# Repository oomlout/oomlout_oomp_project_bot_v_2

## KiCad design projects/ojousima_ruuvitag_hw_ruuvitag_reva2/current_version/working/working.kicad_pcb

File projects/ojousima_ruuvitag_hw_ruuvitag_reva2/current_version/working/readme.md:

# ruuvitag_hw
 
## summary 
* id: ojousima_ruuvitag_hw_ruuvitag_reva2
* user: ojousima
* name: ruuvitag_hw
* board: ruuvitag_reva2
* repo: https://github.com/ojousima/ruuvitag_hw
* src_file_repo_kicad_pcb: ruuvitag_reva2/ruuvitag_reva2.kicad_pcb
* src_file_repo_kicad_pcb_link: https://github.com/ojousima/ruuvitag_hw/tree/master/ruuvitag_reva2/ruuvitag_reva2.kicad_pcb

* src_file_repo_sch: ruuvitag_reva2/ruuvitag_reva2.sch
* src_file_repo_sch_link: https://github.com/ojousima/ruuvitag_hw/tree/master/ruuvitag_reva2/ruuvitag_reva2.sch
* full details link: https://github.com/oomlout/oomlout_oomp_project_bot_v_2/tree/main/projects/ojousima_ruuvitag_hw_ruuvitag_reva2/current_version/working

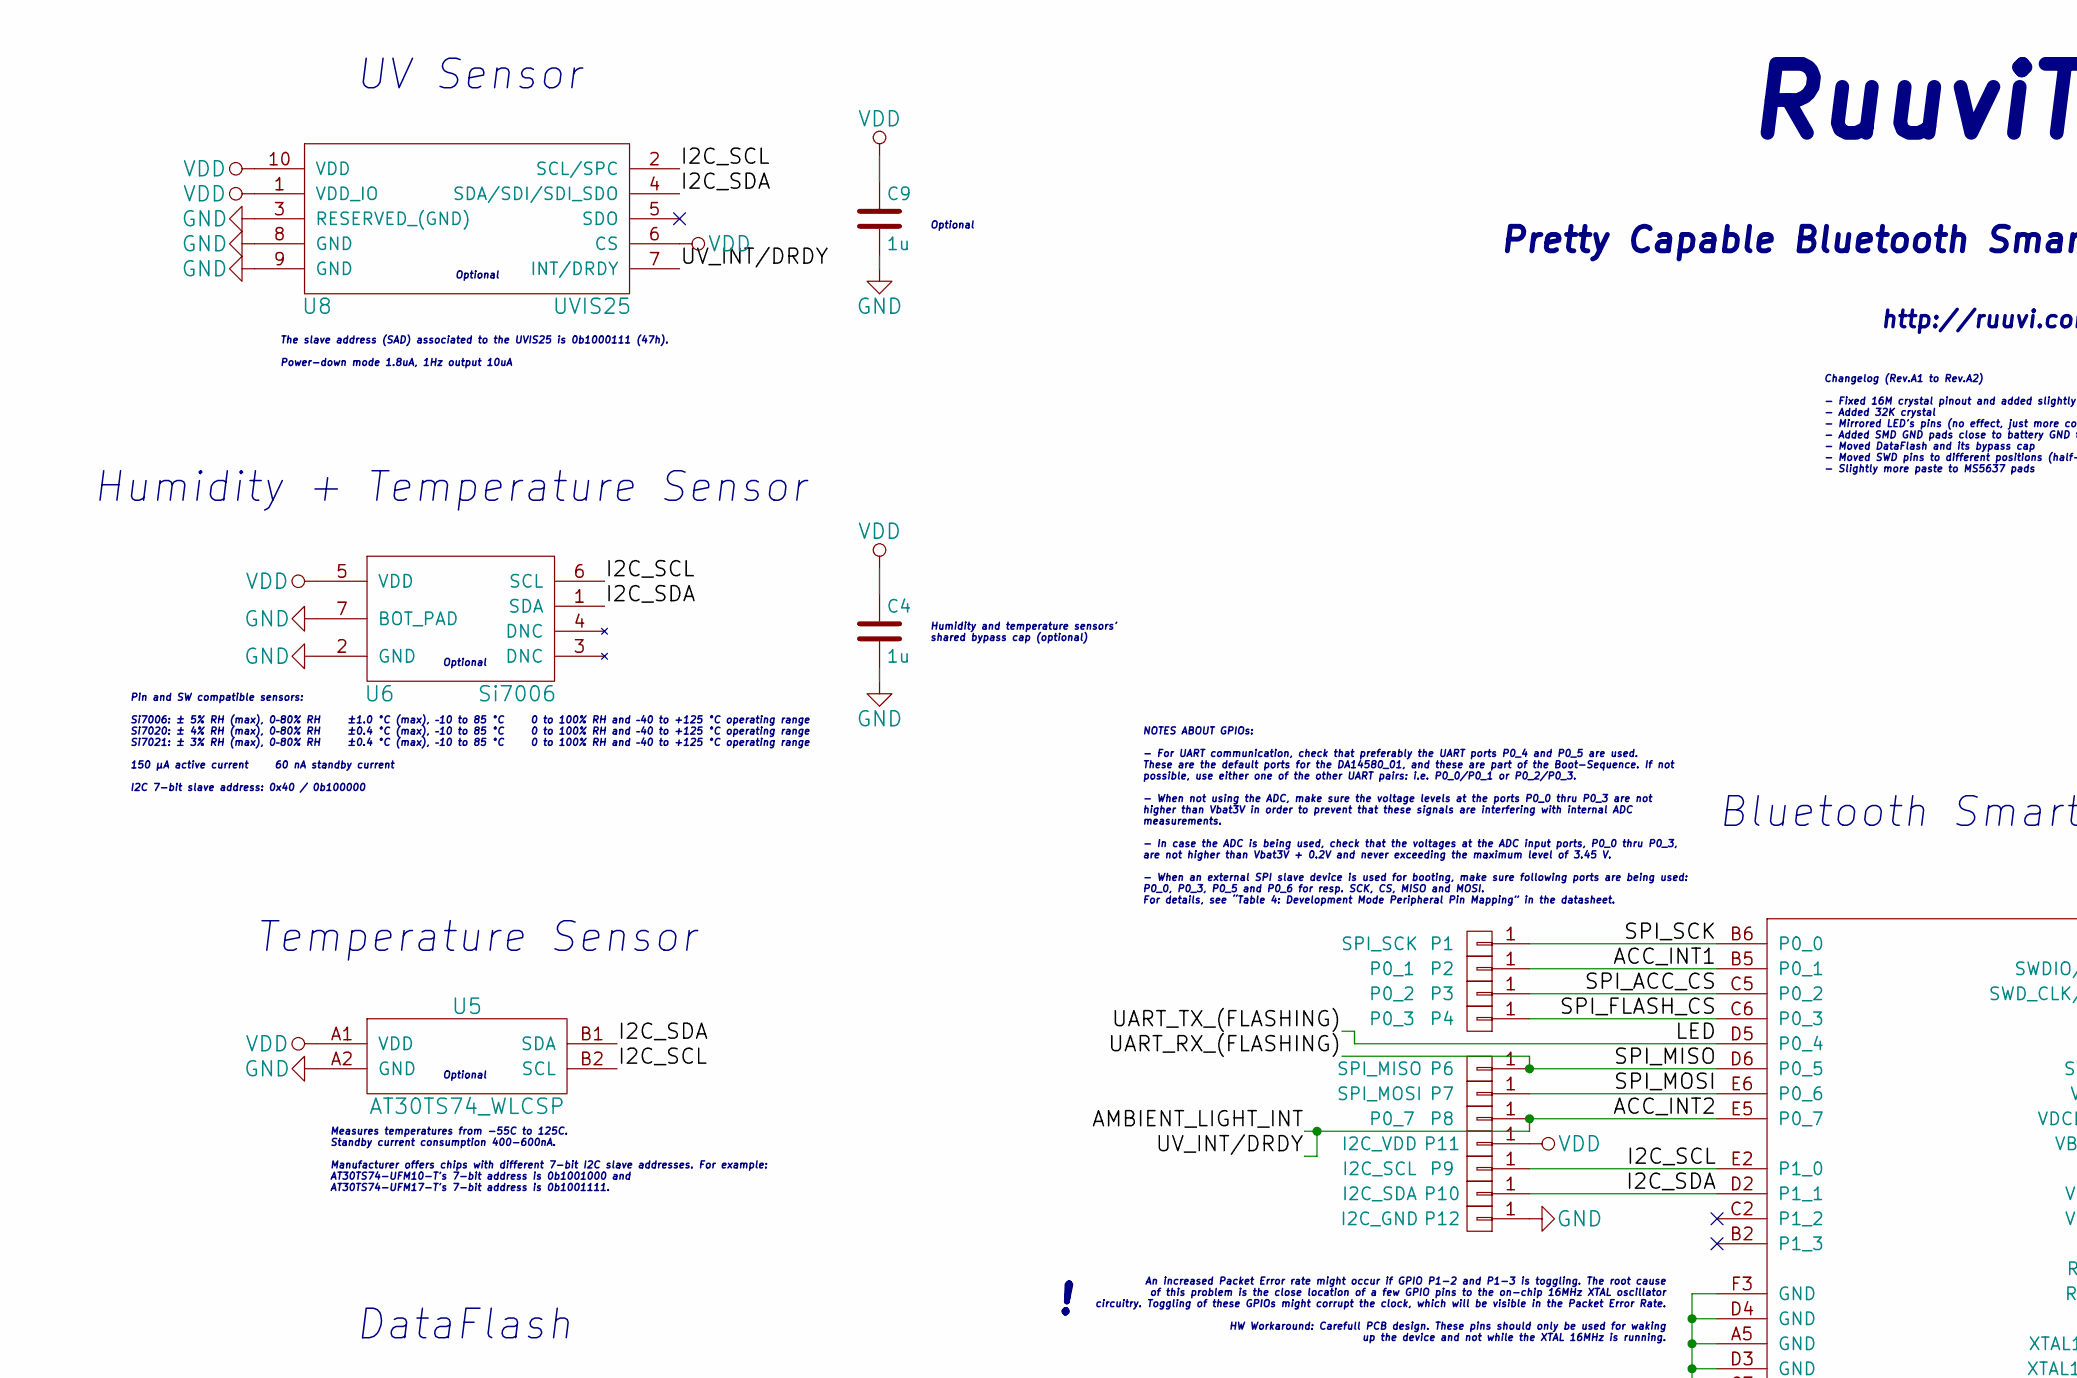
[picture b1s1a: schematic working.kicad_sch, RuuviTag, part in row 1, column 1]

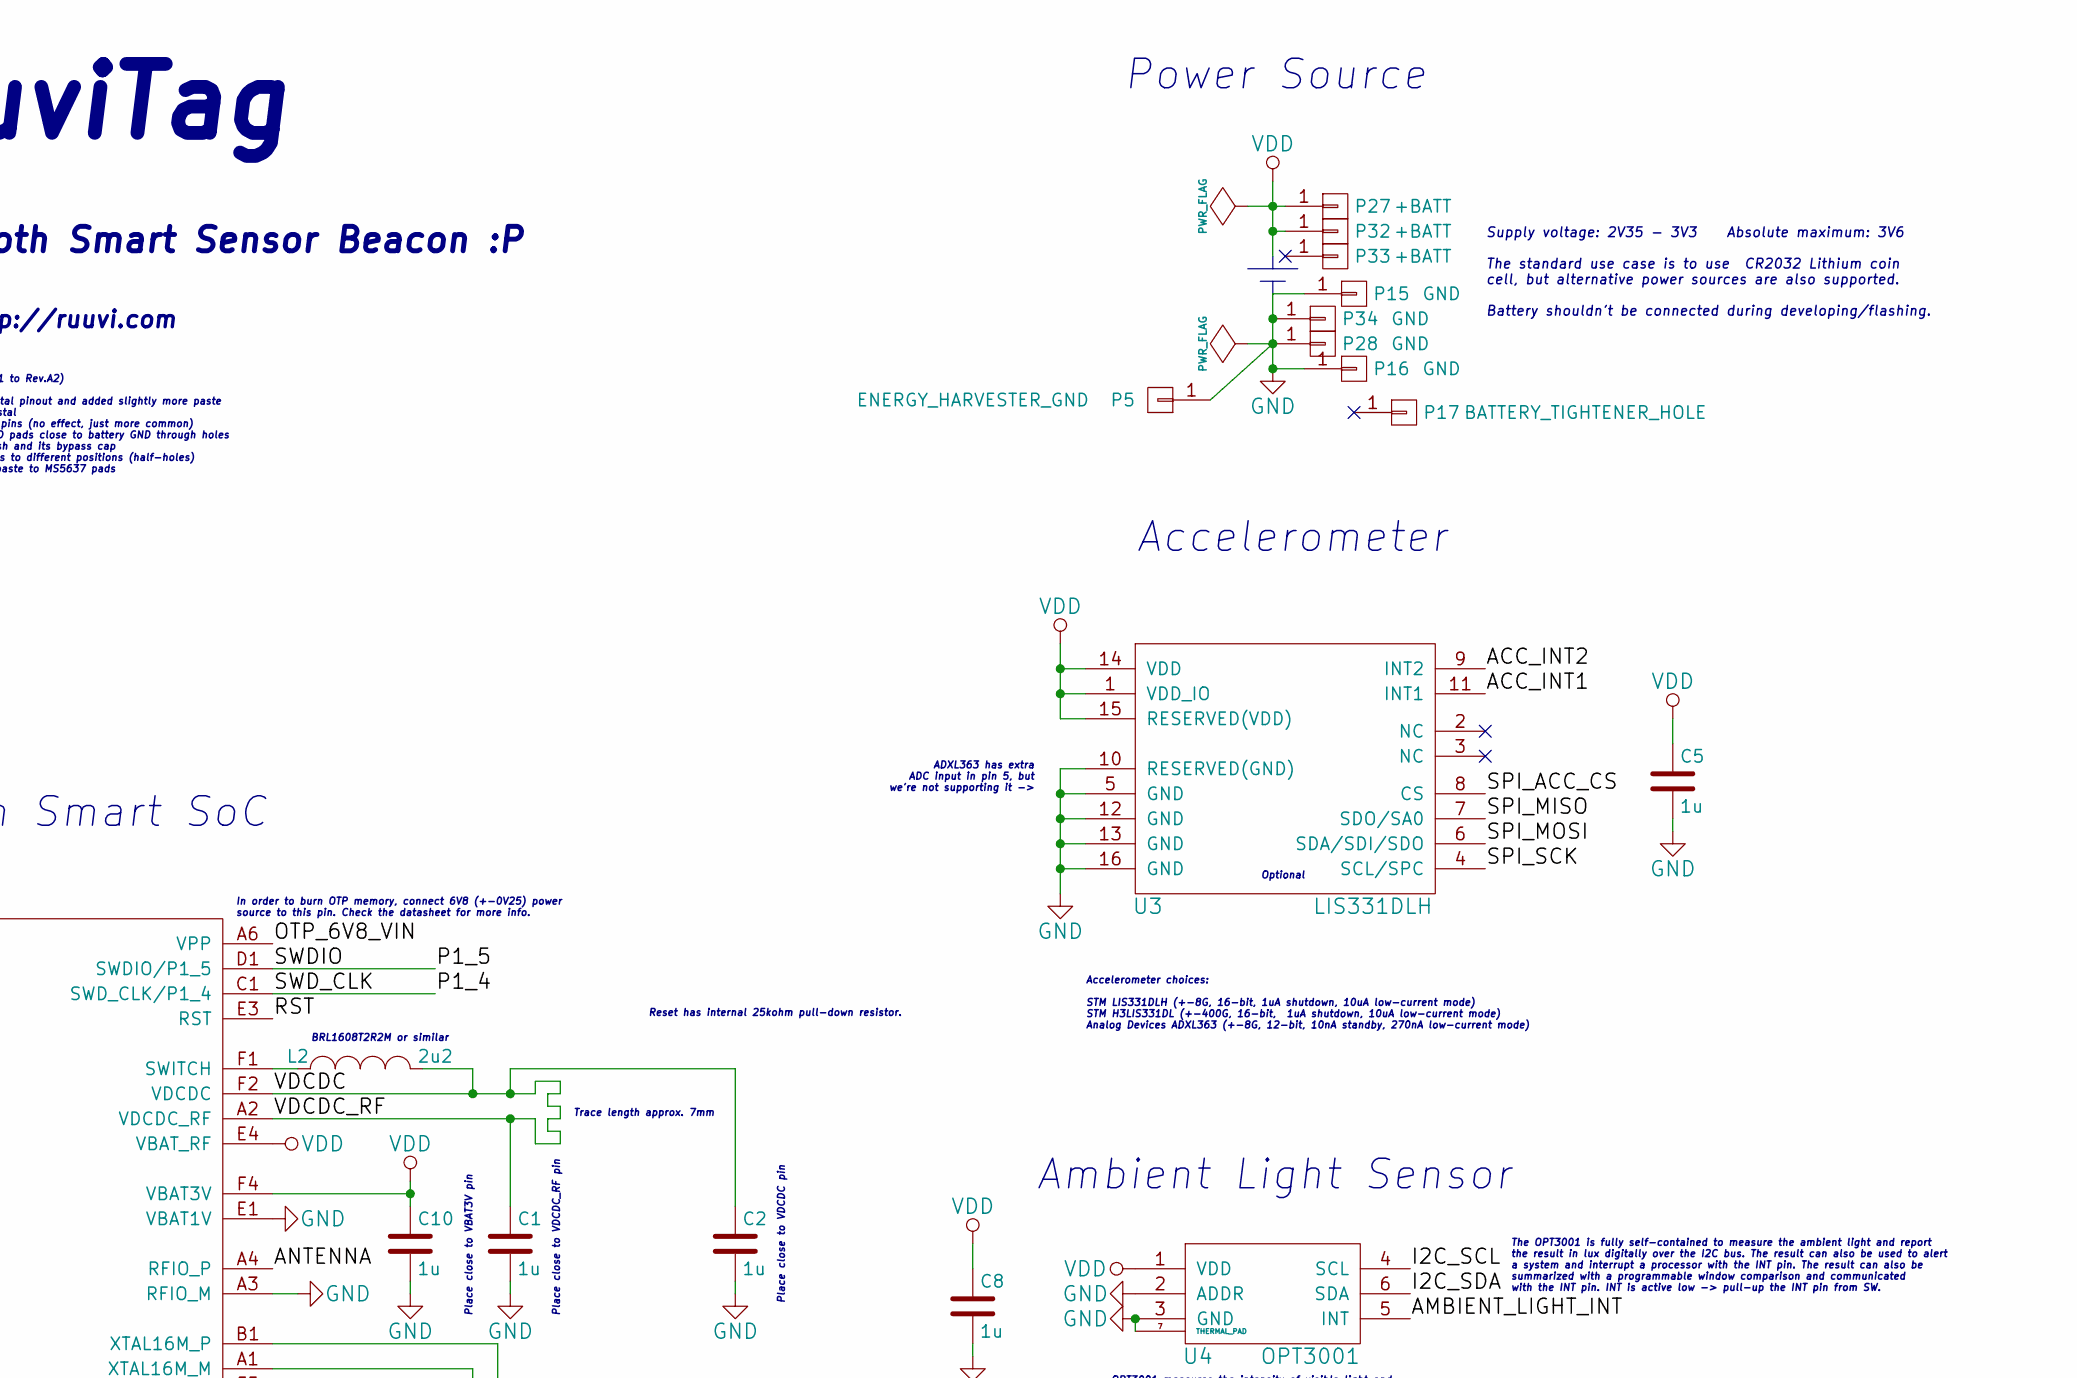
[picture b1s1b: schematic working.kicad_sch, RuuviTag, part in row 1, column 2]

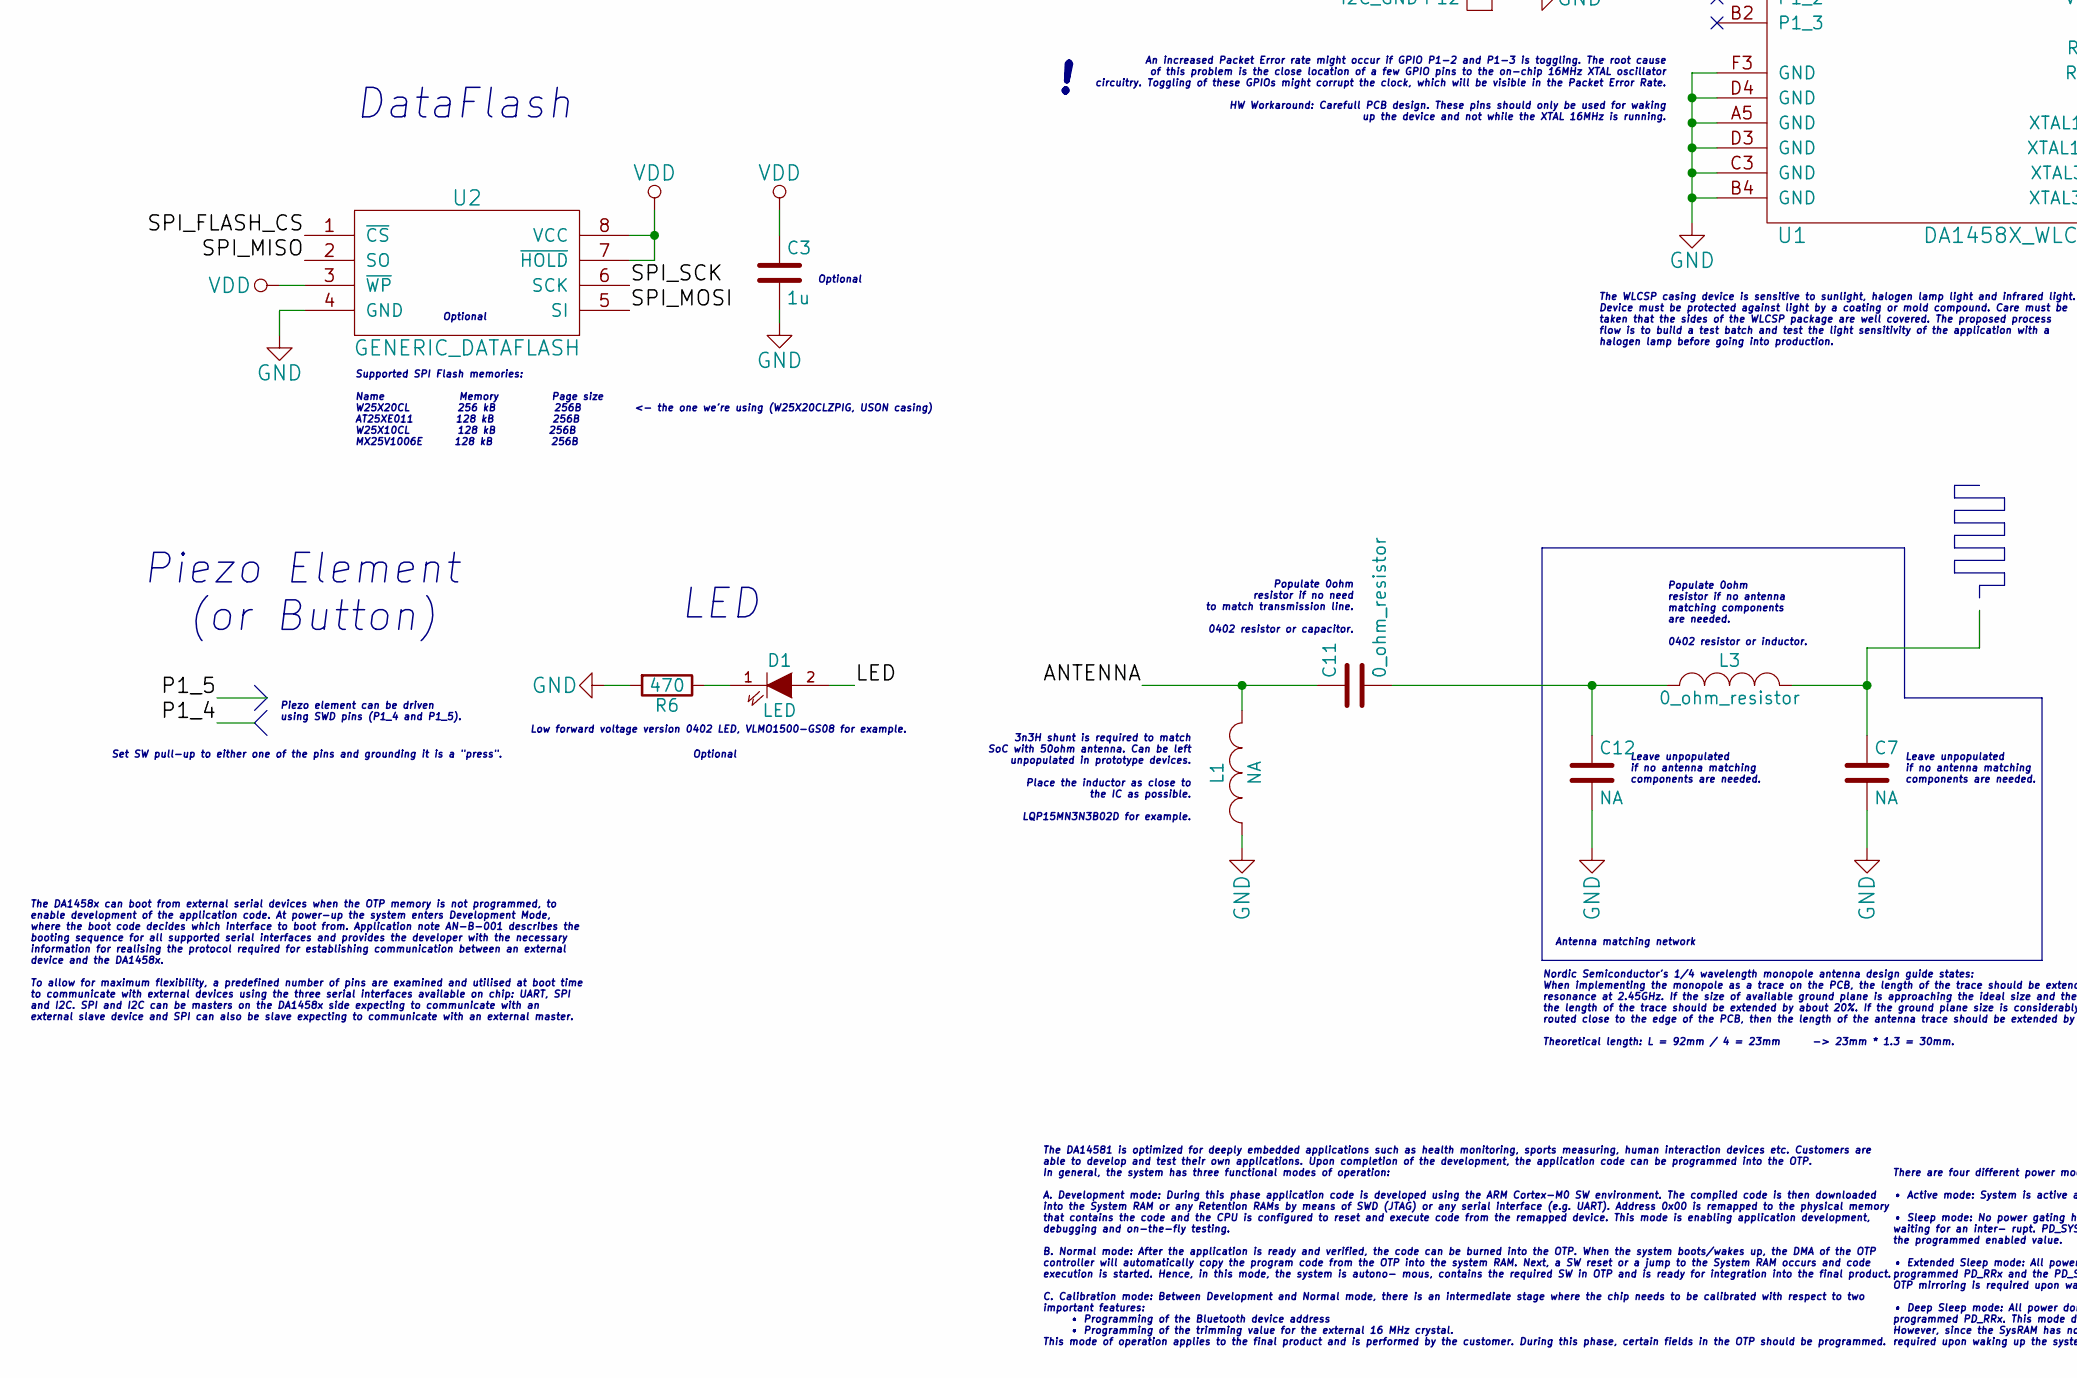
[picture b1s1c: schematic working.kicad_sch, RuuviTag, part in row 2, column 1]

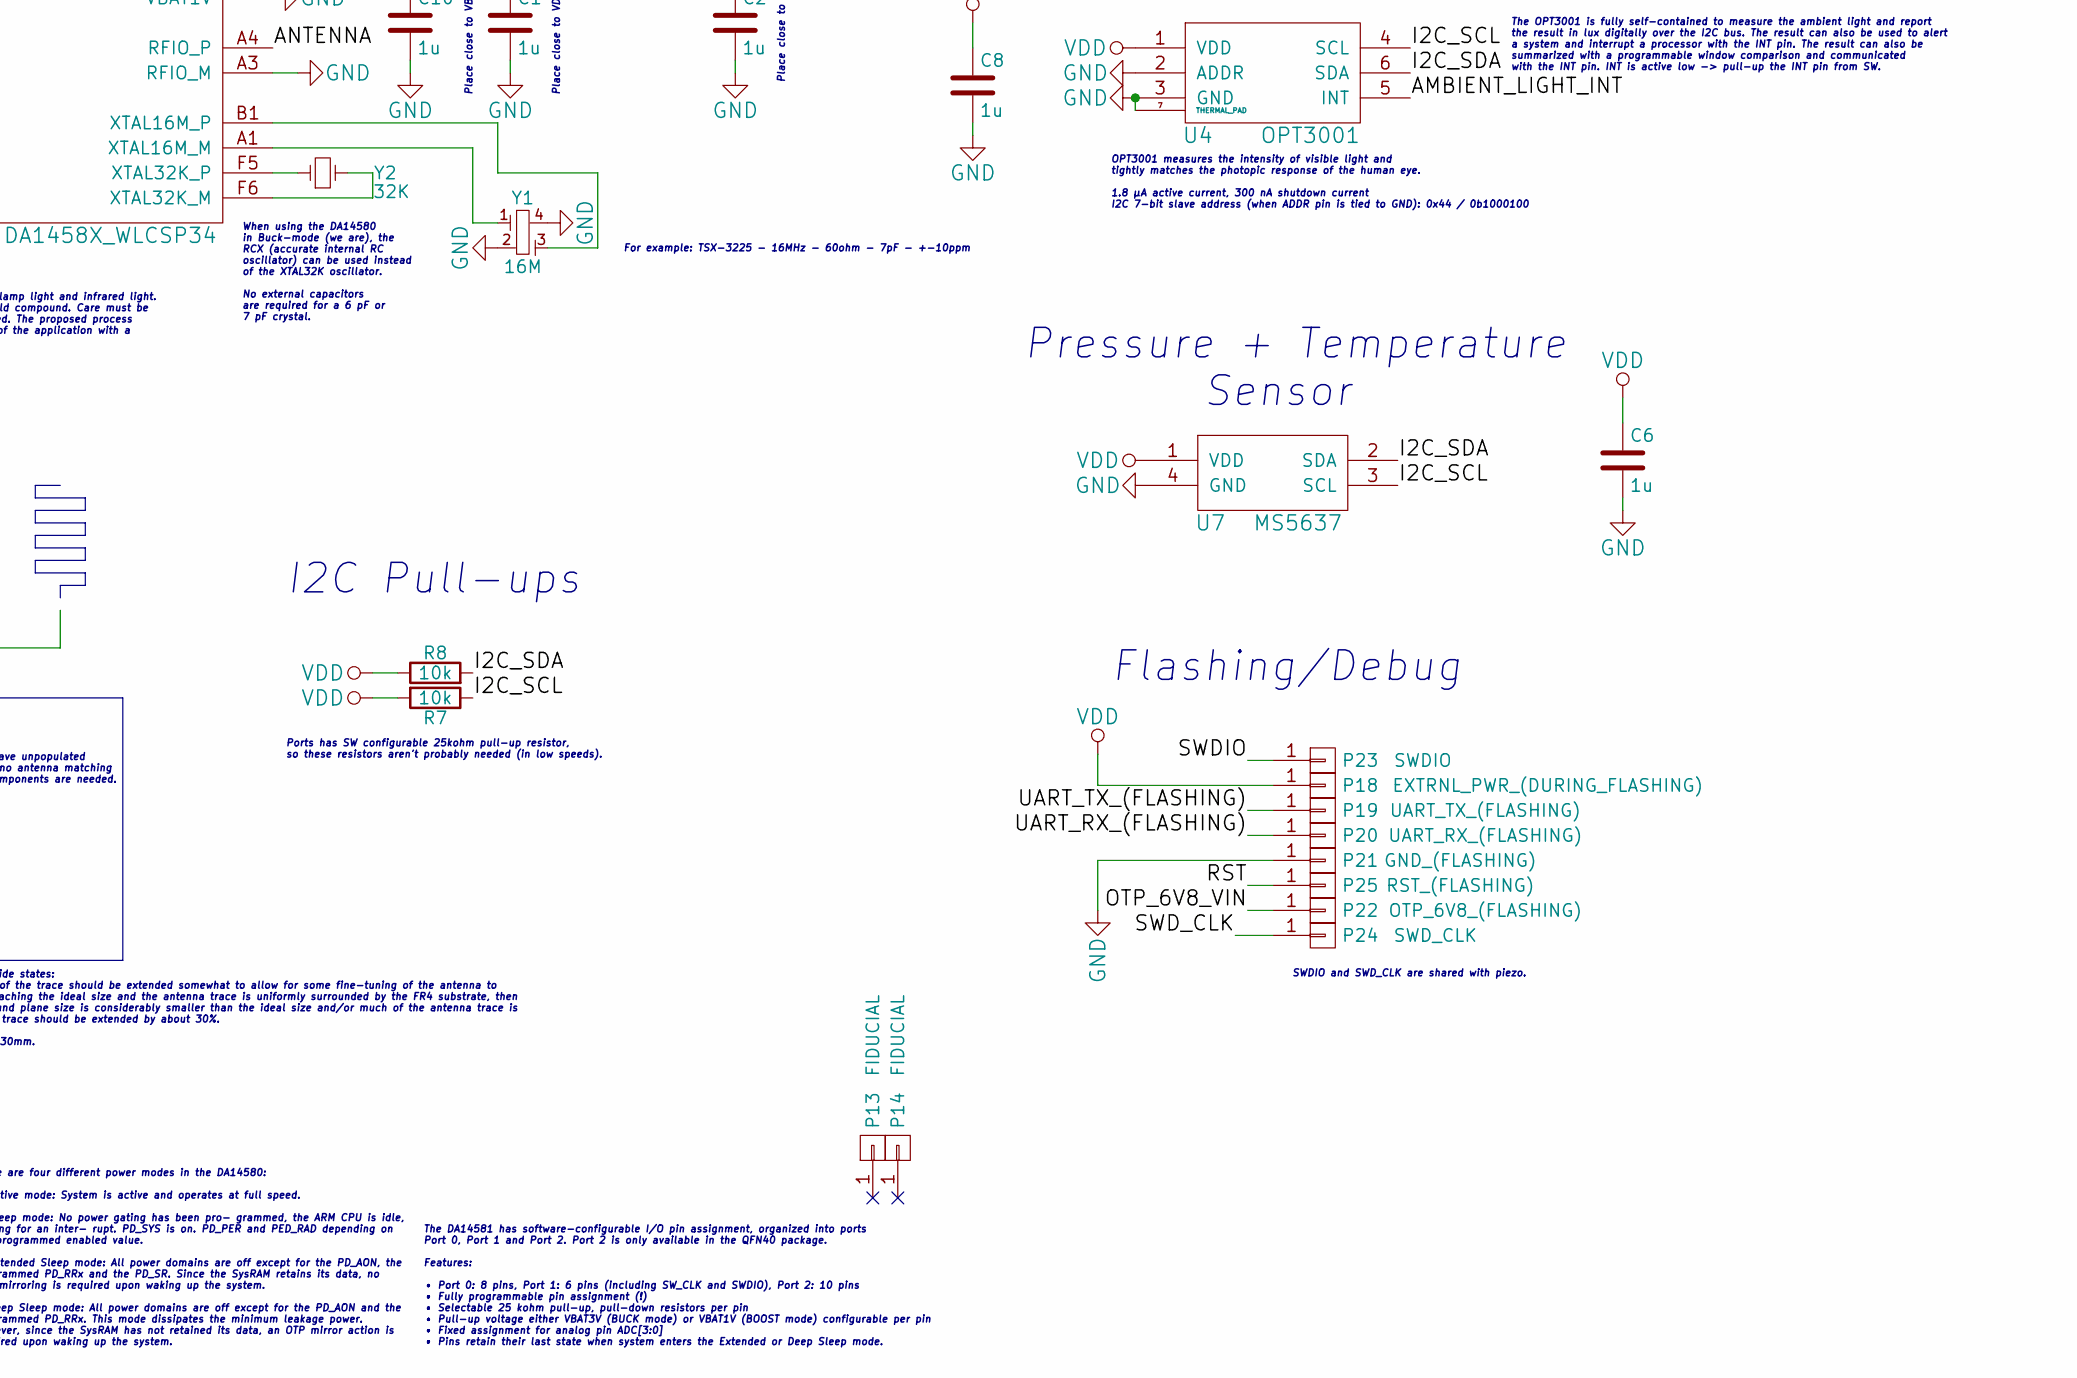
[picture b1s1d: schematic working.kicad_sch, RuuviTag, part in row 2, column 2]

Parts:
C1, C2, C3, C4, C5, C6, C8, C9, C10: 1u; 0402_GENERAL
C7, C12: NA; 0402_GENERAL
C11: 0_ohm_resistor; 0402_GENERAL
D1: LED; 0402_LED
L1: NA; 0402_GENERAL
L2: 2u2; 0603_GENERAL
L3: 0_ohm_resistor; 0402_GENERAL
P1: SPI_SCK; 05MM_PLATED_RECT_HOLE
P2: P0_1; 05MM_PLATED_RECT_HOLE
P3: P0_2; 05MM_PLATED_RECT_HOLE
P4: P0_3; 05MM_PLATED_RECT_HOLE
P5: ENERGY_HARVESTER_GND; WIDE_PLATED_HOLE2
P6: SPI_MISO; 05MM_PLATED_RECT_HOLE
P7: SPI_MOSI; 05MM_PLATED_RECT_HOLE
P8: P0_7; 05MM_PLATED_RECT_HOLE
P9: I2C_SCL; 05MM_PLATED_RECT_HOLE
P10: I2C_SDA; 05MM_PLATED_RECT_HOLE
P11: I2C_VDD; 05MM_PLATED_RECT_HOLE
P12: I2C_GND; 05MM_PLATED_RECT_HOLE
P13, P14: FIDUCIAL; 09MM_PLATED_HOLE
P15, P16, P28, P34: GND; 09MM_PLATED_HOLE
P17: BATTERY_TIGHTENER_HOLE; 09MM_PLATED_HOLE
P18: EXTRNL_PWR_(DURING_FLASHING); 09MM_PLATED_HOLE
P19: UART_TX_(FLASHING); 09MM_PLATED_HOLE
P20: UART_RX_(FLASHING); 09MM_PLATED_HOLE
P21: GND_(FLASHING); 09MM_PLATED_HOLE
P22: OTP_6V8_(FLASHING); 09MM_PLATED_HOLE
P23: SWDIO; 09MM_PLATED_HOLE
P24: SWD_CLK; 09MM_PLATED_HOLE
P25: RST_(FLASHING); 09MM_PLATED_HOLE
P27, P32, P33: +BATT; WIDE_PLATED_HOLE
R6: 470; 0402_GENERAL
R7, R8: 10k; 0402_GENERAL
U1: DA1458X_WLCSP34; WLCSP34
U2: GENERIC_DATAFLASH; USON8_2X3MM
U3: LIS331DLH; LGA16_3X3MM
U4: OPT3001; USON6_2X2MM_WITHTHRMLPAD
U5: AT30TS74_WLCSP; WLCSP4
U6: Si7006; DFN6_3X3MM
U7: MS5637
U8: UVIS25
Y1: 16M; 32X25MM_4PIN_CRYSTAL
Y2: 32K

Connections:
/ACC_INT1: P2.1, U1.B5 (P0_1), U3.11 (INT1)
/ACC_INT2: P8.1, U1.E5 (P0_7), U3.9 (INT2), U4.5 (INT), U8.7 (INT/DRDY)
/ANTENNA: C11.1, L1.2, U1.A4 (RFIO_P)
/I2C_SCL: P9.1, R7.1, U1.E2 (P1_0), U4.4 (SCL), U5.B2 (SCL), U6.6 (SCL), U7.3 (SCL), U8.2 (SCL/SPC)
/I2C_SDA: P10.1, R8.2, U1.D2 (P1_1), U4.6 (SDA), U5.B1 (SDA), U6.1 (SDA), U7.2 (SDA), U8.4 (SDA/SDI/SDI_SDO)
/LED: D1.2 (A), P19.1, U1.D5 (P0_4)
/OTP_6V8_VIN: P22.1, U1.A6 (VPP)
/P1_4: P24.1, U1.C1 (SWD_CLK/P1_4)
/P1_5: P23.1, U1.D1 (SWDIO/P1_5)
/RST: P25.1, U1.E3 (RST)
/SPI_ACC_CS: P3.1, U1.C5 (P0_2), U3.8 (CS)
/SPI_FLASH_CS: P4.1, U1.C6 (P0_3), U2.1 (~CS)
/SPI_MISO: P6.1, P20.1, U1.D6 (P0_5), U2.2 (SO), U3.7 (SDO/SA0)
/SPI_MOSI: P7.1, U1.E6 (P0_6), U2.5 (SI), U3.6 (SDA/SDI/SDO)
/SPI_SCK: P1.1, U1.B6 (P0_0), U2.6 (SCK), U3.4 (SCL/SPC)
/VDCDC: C1.1, C2.1, L2.2, U1.A2 (VDCDC_RF), U1.F2 (VDCDC)
GND: C1.2, C2.2, C3.2, C4.2, C5.2, C6.2, C7.2, C8.2, C9.2, C10.2, C12.2, L1.1, P5.1, P12.1, P15.1, P16.1, P21.1, P28.1, P34.1, R6.2, U1.A3 (RFIO_M), U1.A5 (GND), U1.B4 (GND), U1.C3 (GND), U1.D3 (GND), U1.D4 (GND), U1.E1 (VBAT1V), U1.F3 (GND), U2.4 (GND), U3.5 (GND), U3.10 (RESERVED(GND)), U3.12 (GND), U3.13 (GND), U3.16 (GND), U4.2 (ADDR), U4.3 (GND), U4.7 (THERMAL_PAD), U5.A2 (GND), U6.2 (GND), U6.7 (BOT_PAD), U7.4 (GND), U8.3 (RESERVED_(GND)), U8.8 (GND), U8.9 (GND), Y1.2, Y1.4
unnamed: C7.1, L3.2
unnamed: C11.2, C12.1, L3.1
unnamed: D1.1 (K), R6.1
unnamed: L2.1, U1.F1 (SWITCH)
unnamed: U1.A1 (XTAL16M_M), Y1.1
unnamed: U1.B1 (XTAL16M_P), Y1.3
unnamed: U1.F5 (XTAL32K_P), Y2.1
unnamed: U1.F6 (XTAL32K_M), Y2.2
VDD: C3.1, C4.1, C5.1, C6.1, C8.1, C9.1, C10.1, P11.1, P18.1, P27.1, P32.1, R7.2, R8.1, U1.E4 (VBAT_RF), U1.F4 (VBAT3V), U2.3 (~WP), U2.7 (~HOLD), U2.8 (VCC), U3.1 (VDD_IO), U3.14 (VDD), U3.15 (RESERVED(VDD)), U4.1 (VDD), U5.A1 (VDD), U6.5 (VDD), U7.1 (VDD), U8.1 (VDD_IO), U8.6 (CS), U8.10 (VDD)

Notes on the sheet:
UV Sensor
Accelerometer choices: STM LIS331DLH (+-8G, 16-bit, 1uA shutdown, 10uA low-current mode) STM H3LIS331DL (+-400G, 16-bit, 1uA shutdown, 10uA low-current mode) Analog Devices ADXL363 (+-8G, 12-bit, 10nA standby, 270nA low-current mode)
Trace length approx. 7mm
Place close to VDCDC_RF pin
Temperature Sensor
Low forward voltage version 0402 LED, VLMO1500-GS08 for example.
Changelog (Rev.A1 to Rev.A2) - Fixed 16M crystal pinout and added slightly more paste - Added 32K crystal - Mirrored LED's pins (no effect, just more common) - Added SMD GND pads close to battery GND through holes - Moved DataFlash and its bypass cap - Moved SWD pins to different positions (half-ho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
OPT3001 measures the intensity of visible light and tightly matches the photopic response of the human eye. 1.8 µA active current, 300 nA shutdown current I2C 7-bit slave address (when ADDR pin is tied to GND): 0x44 / 0b1000100
Measures temperatures from -55C to 125C. Standby current consumption 400-600nA. Manufacturer offers chips with different 7-bit I2C slave addresses. For example: AT30TS74-UFM10-T's 7-bit address is 0b1001000 and AT30TS74-UFM17-T's 7-bit address is 0b1001111.
The WLCSP casing device is sensitive to sunlight, halogen lamp light and infrared light. Device must be protected against light by a coating or mold compound. Care must be taken that the sides of the WLCSP package are well covered. The proposed process flow is to build a test batch and test the lig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
The DA14581 has software-configurable I/O pin assignment, organized into ports Port 0, Port 1 and Port 2. Port 2 is only available in the QFN40 package. Features: • Port 0: 8 pins, Port 1: 6 pins (including SW_CLK and SWDIO), Port 2: 10 pins • Fully programmable pin assignment (!) • Selectable 25 k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
Pressure + Temperature Sensor
The OPT3001 is fully self-contained to measure the ambient light and report the result in lux digitally over the I2C bus. The result can also be used to alert a system and interrupt a processor with the INT pin. The result can also be summarized with a programmable window comparison and communicate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
LED
Optional
Nordic Semiconductor's 1/4 wavelength monopole antenna design guide states: When implementing the monopole as a trace on the PCB, the length of the trace should be extended somewhat to allow for some fine-tuning of the antenna to resonance at 2.45GHz. If the size of available ground plane is approa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
Populate 0ohm resistor if no antenna matching components are needed. 0402 resistor or inductor.
The slave address (SAD) associated to the UVIS25 is 0b1000111 (47h). Power-down mode 1.8uA, 1Hz output 10uA
I2C Pull-ups
Accelerometer
Leave unpopulated if no antenna matching components are needed.
DataFlash
The DA1458x can boot from external serial devices when the OTP memory is not programmed, to enable development of the application code. At power-up the system enters Development Mode, where the boot code decides which interface to boot from. Application note AN-B-001 describes the booting sequence 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
Pin and SW compatible sensors: Si7006: ± 5% RH (max), 0–80% RH ±1.0 °C (max), –10 to 85 °C 0 to 100% RH and –40 to +125 °C operating range Si7020: ± 4% RH (max), 0–80% RH ±0.4 °C (max), –10 to 85 °C 0 to 100% RH and –40 to +125 °C operating range Si7021: ± 3% RH (max), 0–80% RH ±0.4 °C (max), –10 t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
The DA14581 is optimized for deeply embedded applications such as health monitoring, sports measuring, human interaction devices etc. Customers are able to develop and test their own applications. Upon completion of the development, the application code can be programmed into the OTP. In general, t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
Piezo element can be driven using SWD pins (P1_4 and P1_5).
RuuviTag
Flashing/Debug
Place close to VBAT3V pin
For example: TSX-3225 - 16MHz - 60ohm - 7pF - +-10ppm
Ports has SW configurable 25kohm pull-up resistor, so these resistors aren't probably needed (in low speeds).
Supported SPI Flash memories: Name Memory Page size W25X20CL 256 kB 256B <- the one we're using (W25X20CLZPIG, USON casing) AT25XE011 128 kB 256B W25X10CL 128 kB 256B MX25V1006E 128 kB 256B
Pretty Capable Bluetooth Smart Sensor Beacon :P
Ambient Light Sensor
Piezo Element (or Button)
Humidity and temperature sensors' shared bypass cap (optional)
ADXL363 has extra ADC input in pin 5, but we're not supporting it ->
NOTES ABOUT GPIOs: - For UART communication, check that preferably the UART ports P0_4 and P0_5 are used. These are the default ports for the DA14580_01, and these are part of the Boot-Sequence. If not possible, use either one of the other UART pairs: i.e. P0_0/P0_1 or P0_2/P0_3. - When not using t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
Supply voltage: 2V35 - 3V3 Absolute maximum: 3V6 The standard use case is to use CR2032 Lithium coin cell, but alternative power sources are also supported. Battery shouldn't be connected during developing/flashing.
Antenna matching network

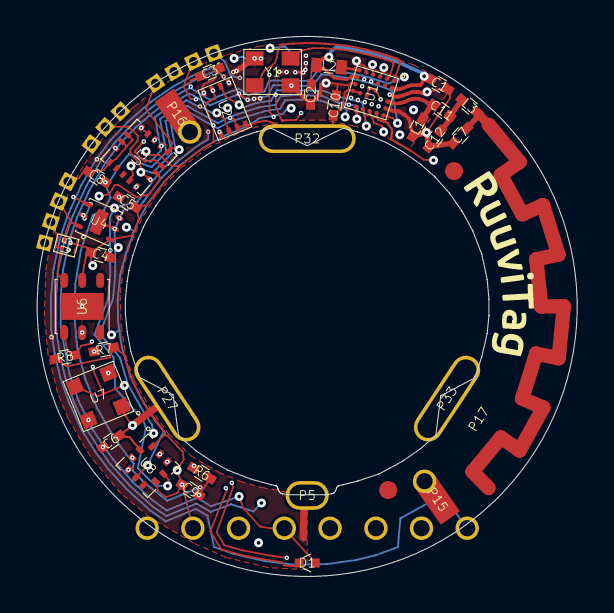
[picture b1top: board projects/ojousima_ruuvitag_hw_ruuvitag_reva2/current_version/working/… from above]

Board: 4 copper layers, 30.0 x 30.0 mm, 59 parts (1 on the bottom side), 26 nets.

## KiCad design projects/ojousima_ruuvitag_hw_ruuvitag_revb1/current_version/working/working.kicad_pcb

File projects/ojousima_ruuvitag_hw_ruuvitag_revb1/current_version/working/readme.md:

# ruuvitag_hw
 
## summary 
* id: ojousima_ruuvitag_hw_ruuvitag_revb1
* user: ojousima
* name: ruuvitag_hw
* board: ruuvitag_revb1
* repo: https://github.com/ojousima/ruuvitag_hw
* src_file_repo_kicad_pcb: ruuvitag_revb1/ruuvitag_revb1.kicad_pcb
* src_file_repo_kicad_pcb_link: https://github.com/ojousima/ruuvitag_hw/tree/master/ruuvitag_revb1/ruuvitag_revb1.kicad_pcb

* src_file_repo_sch: ruuvitag_revb1/ruuvitag_revb1.sch
* src_file_repo_sch_link: https://github.com/ojousima/ruuvitag_hw/tree/master/ruuvitag_revb1/ruuvitag_revb1.sch
* full details link: https://github.com/oomlout/oomlout_oomp_project_bot_v_2/tree/main/projects/ojousima_ruuvitag_hw_ruuvitag_revb1/current_version/working

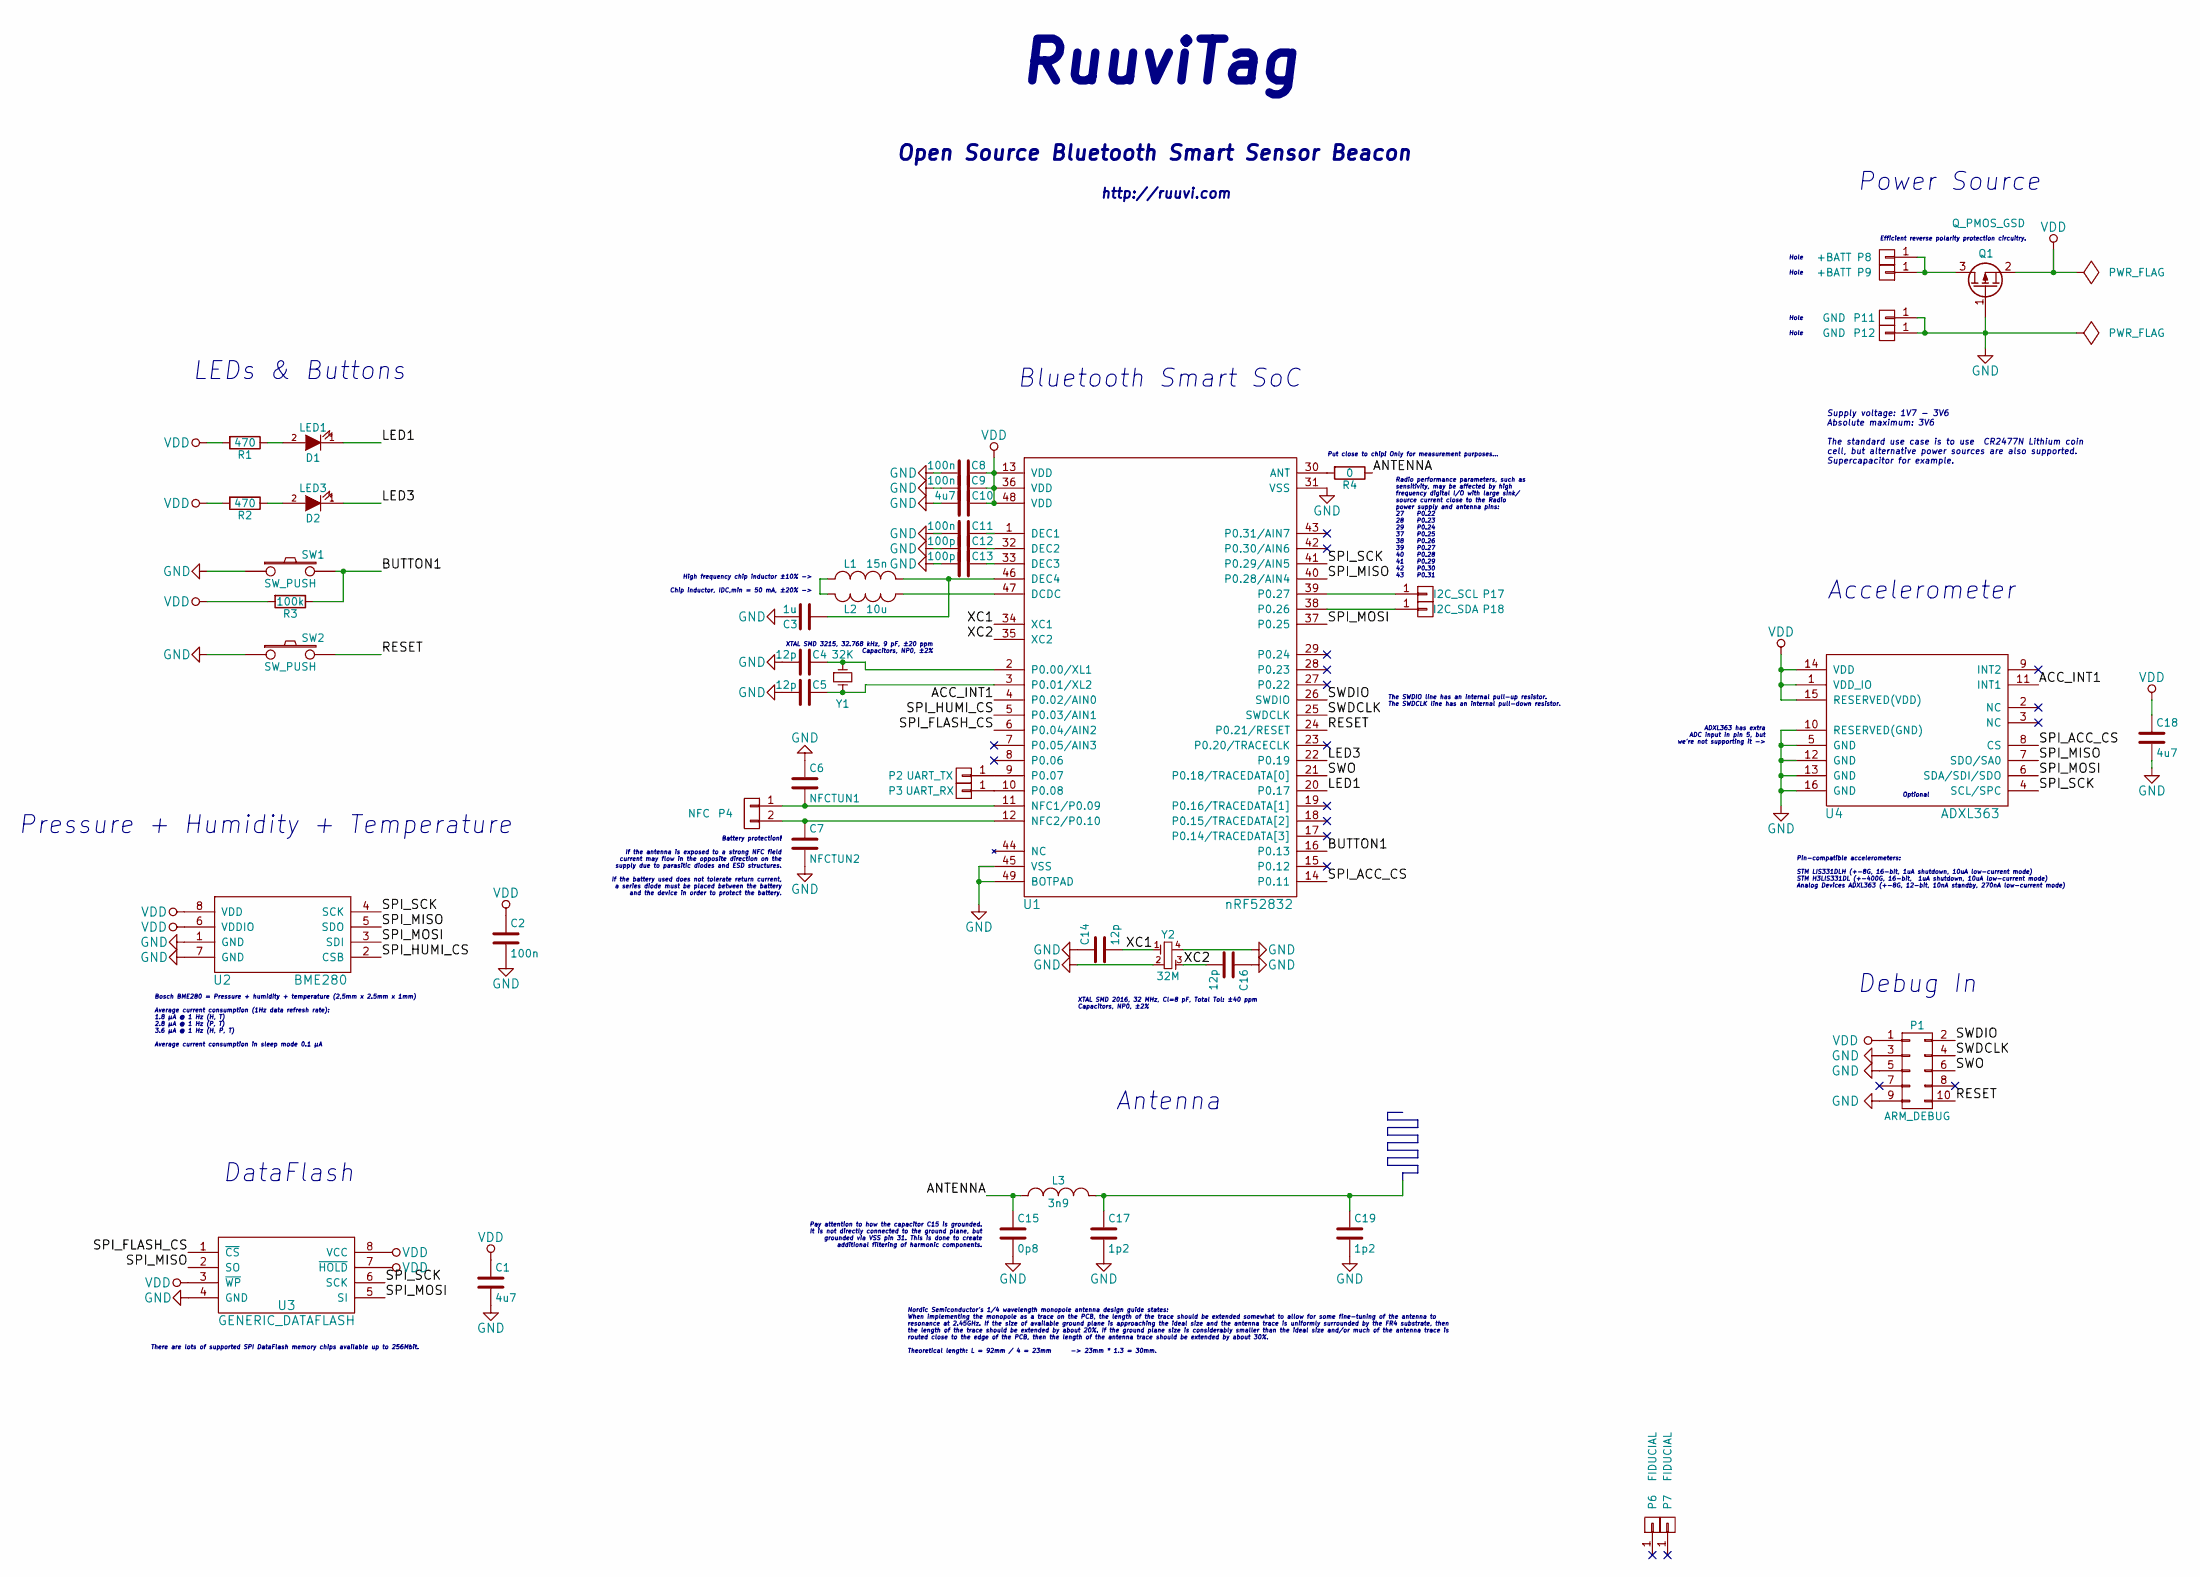
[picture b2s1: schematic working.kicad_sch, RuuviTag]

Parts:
C1, C10, C18: 4u7; 0603_GENERAL
C2, C8, C9, C11: 100n; 0402_GENERAL
C3: 1u; 0402_GENERAL
C4, C5, C14, C16: 12p; 0402_GENERAL
C6: NFCTUN1; 0402_GENERAL
C7: NFCTUN2; 0402_GENERAL
C12, C13: 100p; 0402_GENERAL
C15: 0p8; 0402_GENERAL
C17, C19: 1p2; 0402_GENERAL
D1: LED1; 0402_LED
D2: LED3; 0402_LED
L1: 15n; 0402_GENERAL
L2: 10u; 0603_GENERAL
L3: 3n9; 0402_GENERAL
P1: ARM_DEBUG; ARM_DEBUG_CONNECTOR_10PIN_ALSO_SMD
P2: UART_TX; FIDUCIAL_1MM
P3: UART_RX; FIDUCIAL_1MM
P4: NFC; 2PIN_2MM_PITCH_SMD_PIN_STRIP
P6, P7: FIDUCIAL; FIDUCIAL_1MM
P8, P9: +BATT; 09MM_PLATED_HOLE
P11, P12: GND; 09MM_PLATED_HOLE
P17: I2C_SCL; FIDUCIAL_1MM
P18: I2C_SDA; FIDUCIAL_1MM
Q1: Q_PMOS_GSD; SOT-23
R1, R2: 470; 0402_GENERAL
R3: 100k; 0402_GENERAL
R4: 0; 0603_GENERAL
SW1, SW2: SW_PUSH; SW_SPST_EVQP2
U1: nRF52832; QFN-48_6X6MM_BOTPAD
U2: BME280
U3: GENERIC_DATAFLASH; SOIJ-8_5.3x5.3mm_Pitch1.27mm
U4: ADXL363; LGA16_3X3MM
Y1: 32K; 32X15MM_2PIN_CRYSTAL
Y2: 32M; 32X25MM_4PIN_CRYSTAL

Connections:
/ACC_INT1: U1.4 (P0.02/AIN0), U4.11 (INT1)
/ANTENNA: C15.1, L3.1, R4.1
/BUTTON1: R3.1, SW1.2, U1.16 (P0.13)
/LED1: D1.1 (K), U1.20 (P0.17)
/LED3: D2.1 (K), U1.22 (P0.19)
/RESET: P1.10, SW2.2, U1.24 (P0.21/RESET)
/SPI_ACC_CS: U1.14 (P0.11), U4.8 (CS)
/SPI_FLASH_CS: U1.6 (P0.04/AIN2), U3.1 (~CS)
/SPI_HUMI_CS: U1.5 (P0.03/AIN1), U2.2 (CSB)
/SPI_MISO: U1.40 (P0.28/AIN4), U2.5 (SDO), U3.2 (SO), U4.7 (SDO/SA0)
/SPI_MOSI: U1.37 (P0.25), U2.3 (SDI), U3.5 (SI), U4.6 (SDA/SDI/SDO)
/SPI_SCK: U1.41 (P0.29/AIN5), U2.4 (SCK), U3.6 (SCK), U4.4 (SCL/SPC)
/SWDCLK: P1.4, U1.25 (SWDCLK)
/SWDIO: P1.2, U1.26 (SWDIO)
/SWO: P1.6, U1.21 (P0.18/TRACEDATA[0])
/XC1: C14.2, U1.34 (XC1), Y2.1
/XC2: C16.2, U1.35 (XC2), Y2.3
GND: C1.2, C2.2, C3.2, C4.1, C5.1, C6.1, C7.2, C8.1, C9.1, C10.1, C11.1, C12.1, C13.1, C14.1, C15.2, C16.1, C17.2, C18.2, C19.2, P1.3, P1.5, P1.9, P11.1, P12.1, Q1.1 (G), SW1.1, SW2.1, U1.31 (VSS), U1.45 (VSS), U1.49 (BOTPAD), U2.1 (GND), U2.7 (GND), U3.4 (GND), U4.5 (GND), U4.10 (RESERVED(GND)), U4.12 (GND), U4.13 (GND), U4.16 (GND), Y2.2, Y2.4
unnamed: C3.1, L1.2, U1.46 (DEC4)
unnamed: C4.2, U1.2 (P0.00/XL1), Y1.1
unnamed: C5.2, U1.3 (P0.01/XL2), Y1.2
unnamed: C6.2, P4.1, U1.11 (NFC1/P0.09)
unnamed: C7.1, P4.2, U1.12 (NFC2/P0.10)
unnamed: C11.2, U1.1 (DEC1)
unnamed: C12.2, U1.32 (DEC2)
unnamed: C13.2, U1.33 (DEC3)
unnamed: C17.1, C19.1, L3.2
unnamed: D1.2 (A), R1.1
unnamed: D2.2 (A), R2.1
unnamed: L1.1, L2.2
unnamed: L2.1, U1.47 (DCDC)
unnamed: P2.1, U1.9 (P0.07)
unnamed: P3.1, U1.10 (P0.08)
unnamed: P8.1, P9.1, Q1.3 (D)
unnamed: P17.1, U1.39 (P0.27)
unnamed: P18.1, U1.38 (P0.26)
unnamed: R4.2, U1.30 (ANT)
VDD: C1.1, C2.1, C8.2, C9.2, C10.2, C18.1, P1.1, Q1.2 (S), R1.2, R2.2, R3.2, U1.13 (VDD), U1.36 (VDD), U1.48 (VDD), U2.6 (VDDIO), U2.8 (VDD), U3.3 (~WP), U3.7 (~HOLD), U3.8 (VCC), U4.1 (VDD_IO), U4.14 (VDD), U4.15 (RESERVED(VDD))

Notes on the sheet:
Battery protection! If the antenna is exposed to a strong NFC field current may flow in the opposite direction on the supply due to parasitic diodes and ESD structures. If the battery used does not tolerate return current, a series diode must be placed between the battery and the device in order to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
High frequency chip inductor ±10% -> Chip inductor, IDC,min = 50 mA, ±20% ->
Optional
Efficient reverse polarity protection circuitry.
Hole
Pressure + Humidity + Temperature
Supply voltage: 1V7 - 3V6 Absolute maximum: 3V6 The standard use case is to use CR2477N Lithium coin cell, but alternative power sources are also supported. Supercapacitor for example.
Nordic Semiconductor's 1/4 wavelength monopole antenna design guide states: When implementing the monopole as a trace on the PCB, the length of the trace should be extended somewhat to allow for some fine-tuning of the antenna to resonance at 2.45GHz. If the size of available ground plane is approa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
Bosch BME280 = Pressure + humidity + temperature (2,5mm x 2.5mm x 1mm) Average current consumption (1Hz data refresh rate): 1.8 μA @ 1 Hz (H, T) 2.8 μA @ 1 Hz (P, T) 3.6 μA @ 1 Hz (H, P, T) Average current consumption in sleep mode 0.1 μA
Power Source
The SWDIO line has an internal pull-up resistor. The SWDCLK line has an internal pull-down resistor.
RuuviTag
Bluetooth Smart SoC
LEDs & Buttons
http://ruuvi.com
XTAL SMD 2016, 32 MHz, Cl=8 pF, Total Tol: ±40 ppm Capacitors, NP0, ±2%
XTAL SMD 3215, 32.768 kHz, 9 pF, ±20 ppm Capacitors, NP0, ±2%
Open Source Bluetooth Smart Sensor Beacon
DataFlash
Antenna
Put close to chip! Only for measurement purposes...
There are lots of supported SPI DataFlash memory chips available up to 256Mbit.
Pin-compatible accelerometers: STM LIS331DLH (+-8G, 16-bit, 1uA shutdown, 10uA low-current mode) STM H3LIS331DL (+-400G, 16-bit, 1uA shutdown, 10uA low-current mode) Analog Devices ADXL363 (+-8G, 12-bit, 10nA standby, 270nA low-current mode)
Accelerometer
Pay attention to how the capacitor C15 is grounded. It is not directly connected to the ground plane, but grounded via VSS pin 31. This is done to create additional filtering of harmonic components.
Radio performance parameters, such as sensitivity, may be affected by high frequency digital I/O with large sink/ source current close to the Radio power supply and antenna pins: 27 P0.22 28 P0.23 29 P0.24 37 P0.25 38 P0.26 39 P0.27 40 P0.28 41 P0.29 42 P0.30 43 P0.31
ADXL363 has extra ADC input in pin 5, but we're not supporting it ->
Debug In

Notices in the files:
projects/ojousima_ruuvitag_hw_ruuvitag_reva2/current_version/working/working.kicad_sch:
http://creativecommons.org/licenses/by-sa/4.0
License: Attribution-ShareAlike 4.0 International (CC BY-SA 4.0)
projects/ojousima_ruuvitag_hw_ruuvitag_revb1/current_version/working/working.kicad_sch:
License: http://creativecommons.org/licenses/by-sa/4.0
